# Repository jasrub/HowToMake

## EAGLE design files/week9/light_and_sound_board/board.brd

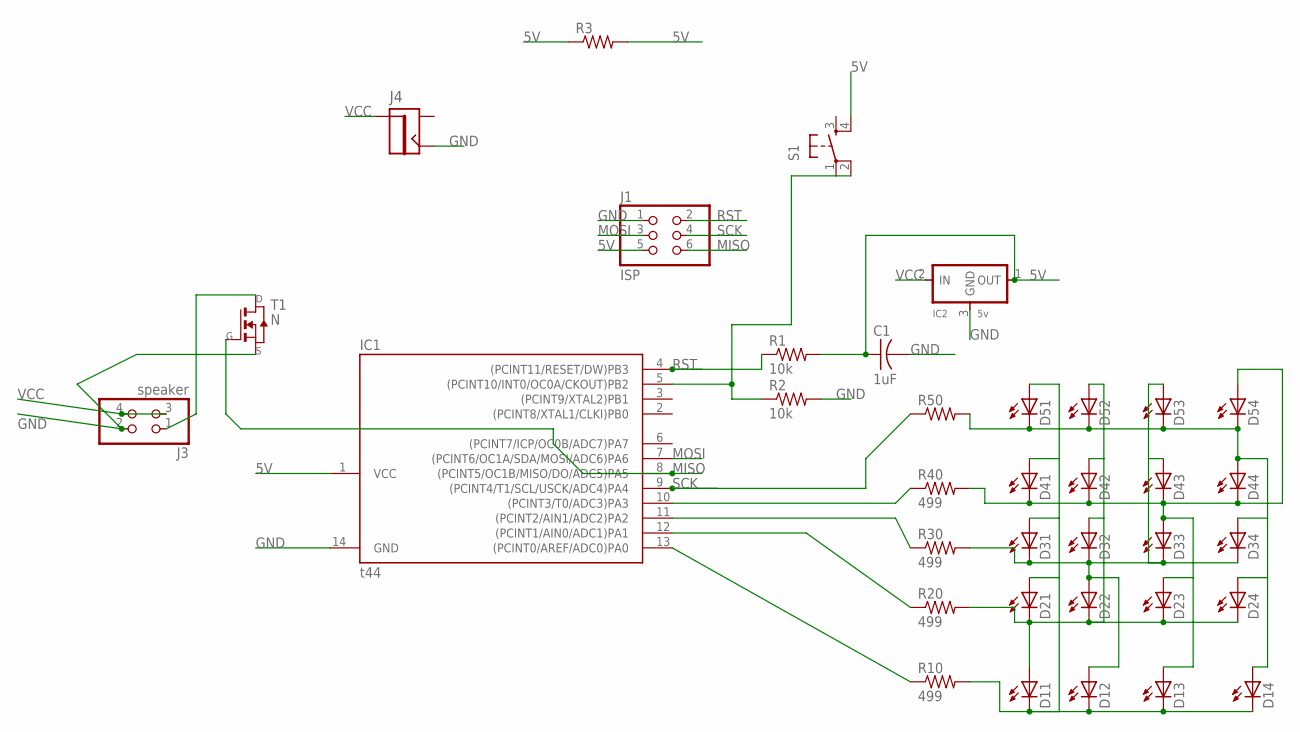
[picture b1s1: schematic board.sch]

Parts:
C1: 1uF; C1206FAB
D11, D12, D13, D14, D21, D22, D23, D24, D31, D32, D33, D34, D41, D42, D43, D44, D51, D52, D53, D54: LEDFAB1206; LED1206FAB
IC1: t44; SOIC14
IC2: 5v; SOT23
J1: ISP; 2X03SMD
J3: speaker; 2X02SMD
J4: JACK2.1MM; JACK_2.1MM
R1, R2: 10k; R1206FAB
R3, R50: RES-US1206FAB; R1206FAB
R10, R20, R30, R40: 499; R1206FAB
S1: 6MM_SWITCH6MM_SWITCH; 6MM_SWITCH
T1: N; SOT-23

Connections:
5V: C1.1, IC1.1 (VCC), IC2.1 (OUT), J1.5, R1.2, R3.1, R3.2, S1.4 (S1)
GND: C1.2, IC1.14 (GND), IC2.3 (GND), J1.1, J3.2, J4.CONTACT, R2.2, T1.2 (S)
MISO: IC1.8 ((PCINT5/OC1B/MISO/DO/ADC5)PA5), J1.6, T1.3 (G)
MOSI: IC1.7 ((PCINT6/OC1A/SDA/MOSI/ADC6)PA6), J1.3
unnamed: IC1.13 ((PCINT0/AREF/ADC0)PA0), R10.1
unnamed: IC1.12 ((PCINT1/AIN0/ADC1)PA1), R20.1
unnamed: IC1.11 ((PCINT2/AIN1/ADC2)PA2), R30.1
unnamed: IC1.10 ((PCINT3/T0/ADC3)PA3), R40.1
unnamed: D11.2 (C), D12.2 (C), D13.2 (C), D14.2 (C), D21.1 (A), D31.1 (A), D41.1 (A), D51.1 (A), R10.2
unnamed: D11.1 (A), D21.2 (C), D22.2 (C), D23.2 (C), D24.2 (C), D32.1 (A), D42.1 (A), D52.1 (A), R20.2
unnamed: J3.1, T1.1 (D)
unnamed: D12.1 (A), D22.1 (A), D31.2 (C), D32.2 (C), D33.2 (C), D34.2 (C), D43.1 (A), D53.1 (A), R30.2
unnamed: D13.1 (A), D23.1 (A), D33.1 (A), D41.2 (C), D42.2 (C), D43.2 (C), D44.2 (C), D54.1 (A), R40.2
unnamed: D14.1 (A), D24.1 (A), D34.1 (A), D44.1 (A), D51.2 (C), D52.2 (C), D53.2 (C), D54.2 (C), R50.2
unnamed: IC1.5 ((PCINT10/INT0/OC0A/CKOUT)PB2), R2.1, S1.2 (P1)
RST: IC1.4 ((PCINT11/RESET/DW)PB3), J1.2, R1.1
SCK: IC1.9 ((PCINT4/T1/SCL/USCK/ADC4)PA4), J1.4, R50.1
VCC: IC2.2 (IN), J3.3, J3.4, J4.PIN

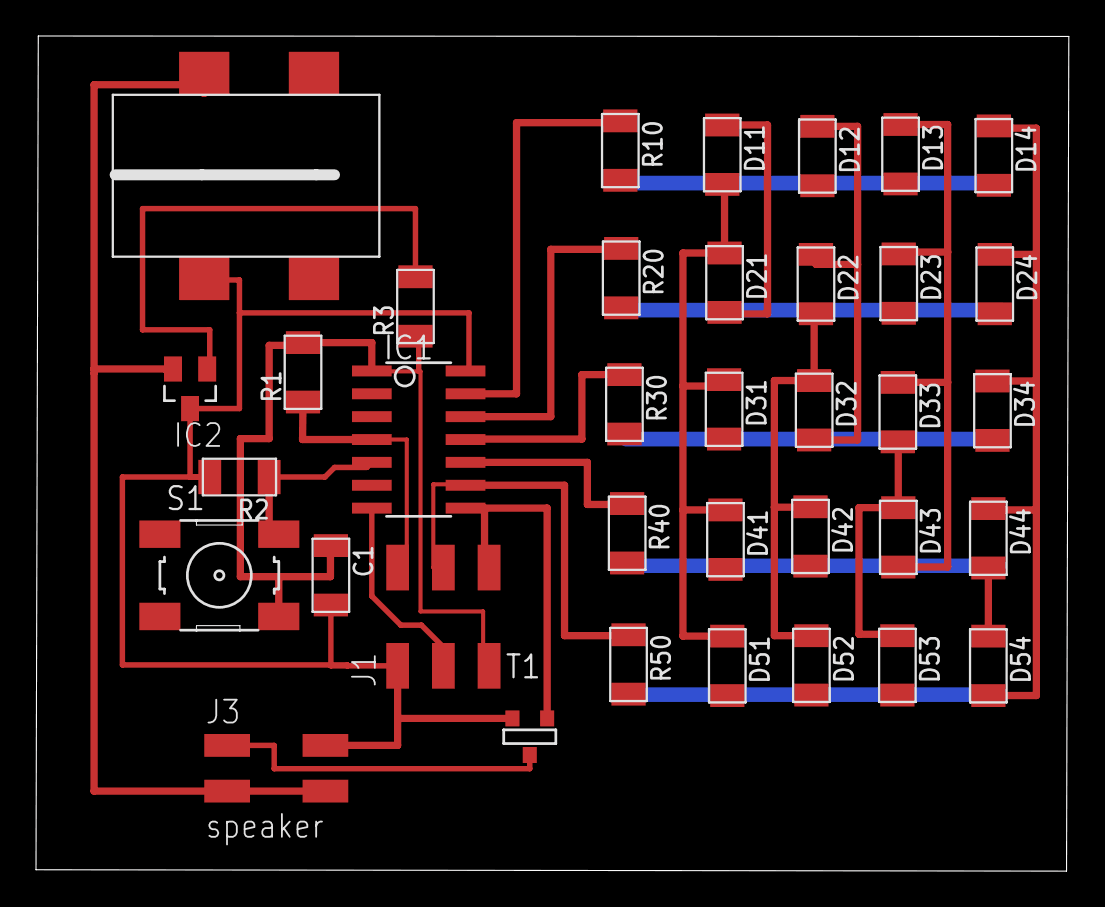
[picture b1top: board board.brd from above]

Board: 2 copper layers, 57.4 x 46.4 mm, 36 parts (0 on the bottom side), 18 nets.

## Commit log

2015-09-22 add index.html
2015-09-22 add hayush
2015-09-22 initail commit
2015-09-23 Website editing
2015-09-23 web edit
2015-11-14 uploading all website files
2015-11-14 adding week9 files
2015-11-14 move files here
2015-12-16 adding files
